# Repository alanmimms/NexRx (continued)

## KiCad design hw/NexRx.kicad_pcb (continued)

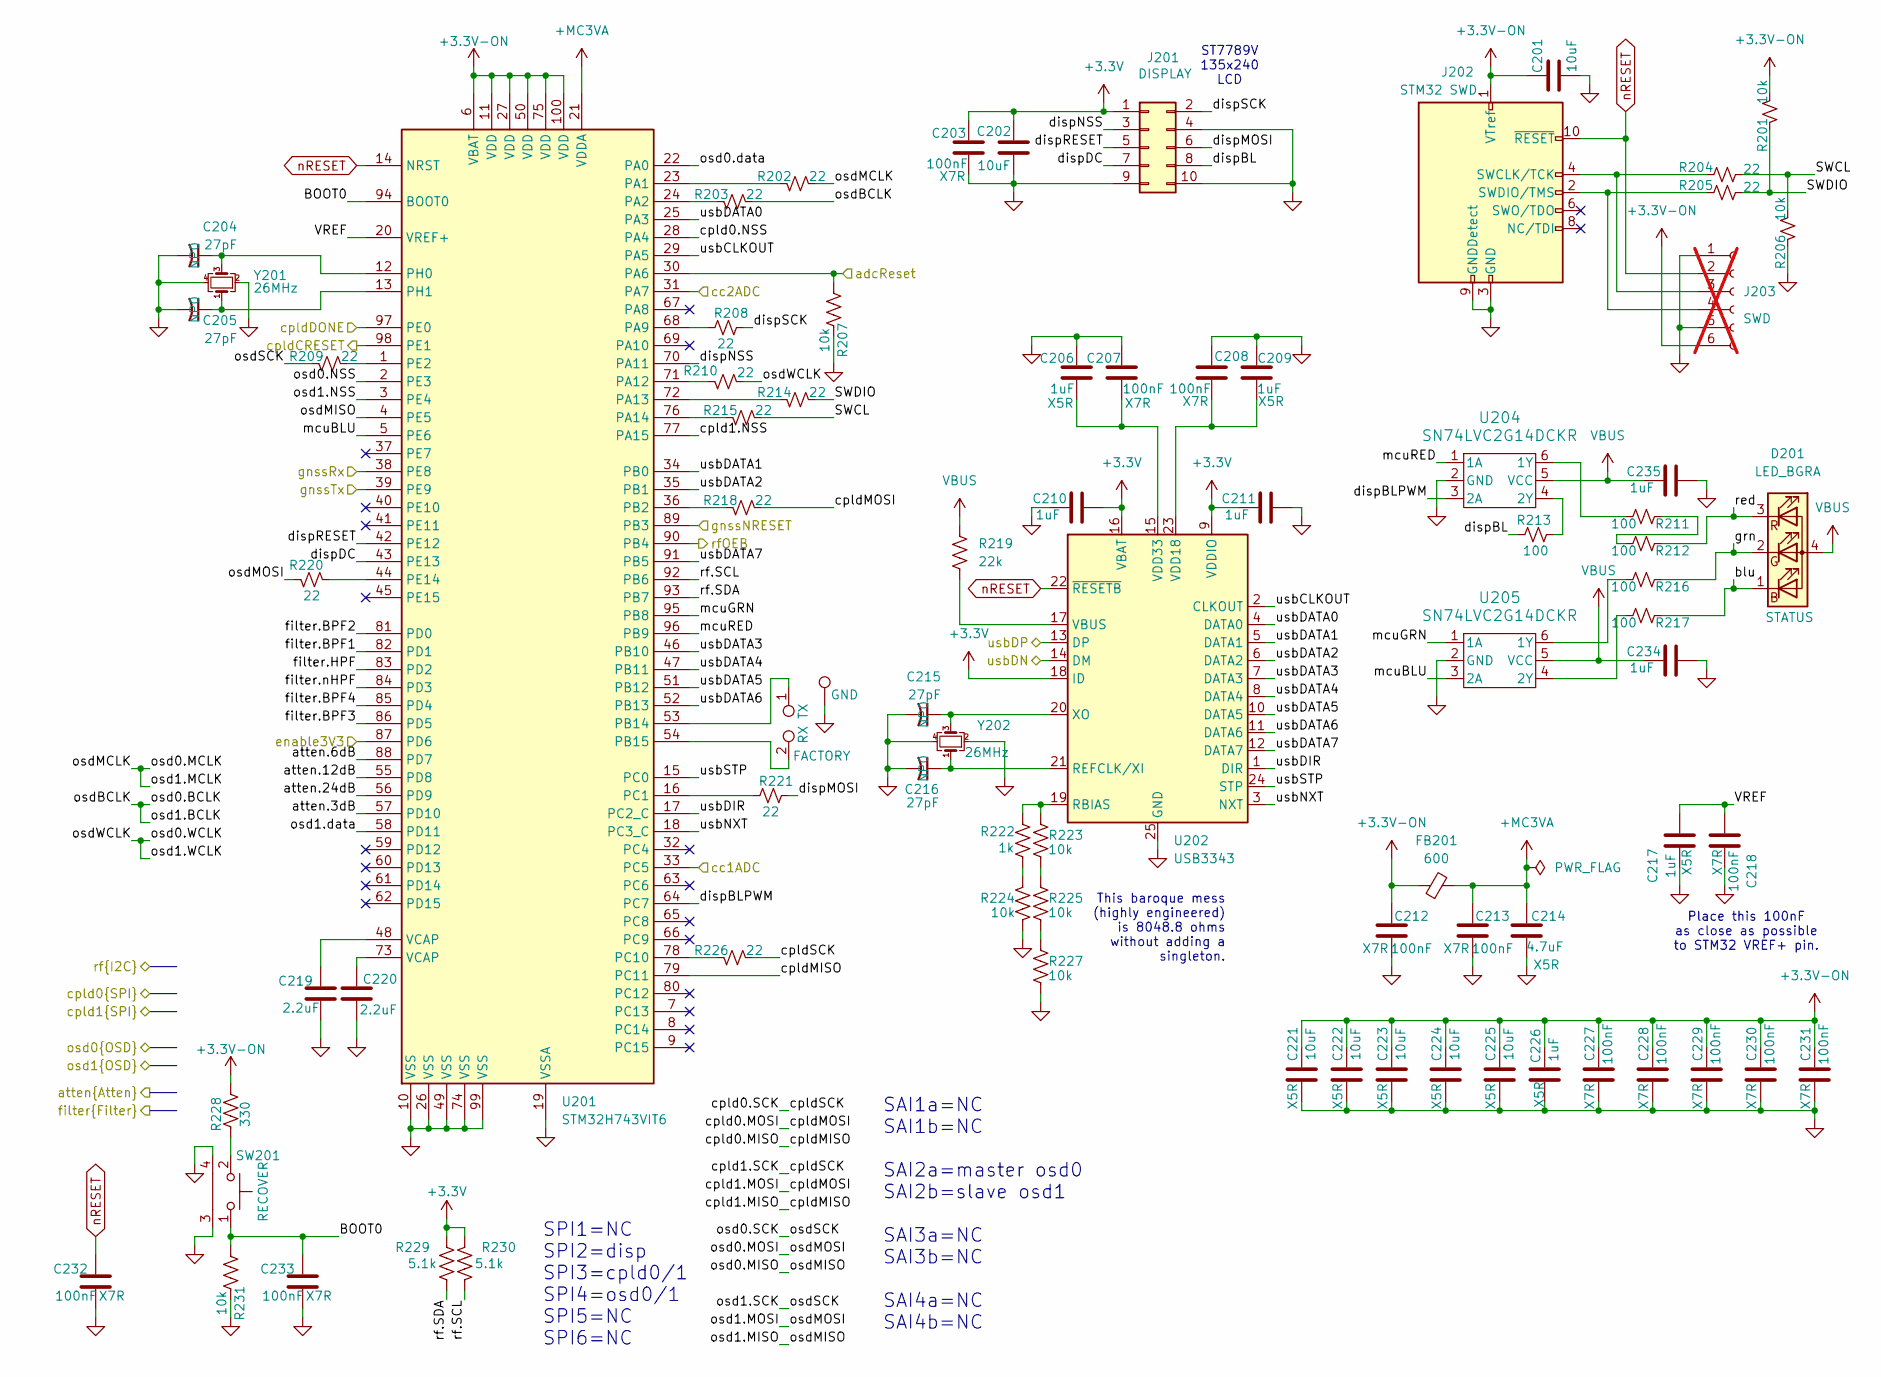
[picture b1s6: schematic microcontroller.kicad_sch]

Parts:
C201: 10uF; C_0402_1005Metric; MPN CL05A106MP6NUN8; LCSC_PN C76991
C202, C221, C222, C223, C224, C225: 10uF; C_0402_1005Metric; Mouser Part Number 187-CL05A106MP6NUN8
C203, C207, C208, C212, C213, C231: 100nF; C_0402_1005Metric; MPN GCM155R71H104KE02D; LCSC_PN C307331
C204: 27pF; C_0402_1005Metric; MPN 04023A270JAT2A; LCSC_PN C1557
C205, C215, C216: 27pF; C_0402_1005Metric; MPN 04023A270JAT2A; Mouser Part Number 581-04023A270JAT2A
C206, C209, C210, C211, C234, C235: 1uF; C_0402_1005Metric; Mouser Part Number 81-GRM155R61E105MA2D
C214: 4.7uF; C_0402_1005Metric; MPN CM05X5R475M10AH; LCSC_PN C23733
C217, C226: 1uF; C_0402_1005Metric; MPN GRM155R61E105MA12D; LCSC_PN C77009
C218, C227, C228, C229, C230, C232, C233: 100nF; C_0402_1005Metric; Mouser Part Number 81-GCM155R71H104KE2D
C219, C220: 2.2uF; C_0402_1005Metric; MPN TMK105CBJ225MV-F; LCSC_PN C12530
D201: LED_BGRA; WL-SFCD_0606; Mouser_PN 941-UHD1AA3K3E3V53Z3
FB201: 600; L_0603_1608Metric; MPN MI0603J601R-10; LCSC_PN C1006
J201: Conn_01x05_Pin; IDC-Header_2x05_P2.54mm_Vertical_SMD; LCSC_PN C32713285
J202: FTSH-105-01-L-DV-K; FTSH10501LDVK; MPN FTSH-105-01-L-DV-K; LCSC_PN C5155080
J203: SWD; PinHeader_1x06_P2.54mm_Vertical; not fitted
R201, R206, R207, R223, R224, R225, R227, R231: 10k; R_0402_1005Metric; MPN RT0402BRD0710KL; LCSC_PN C283961
R202, R203: 22; R_0402_1005Metric; MPN 560112110216; LCSC_PN C25092
R204, R205, R208, R209, R210, R214, R215, R218, R220, R221, R226: 22; R_0402_1005Metric; MPN 560112110216; JLCPCBpn C4258780
R211, R212, R213, R216, R217: 100; R_0402_1005Metric; MPN MCS04020C1000FE000; Mouser Part Number 594-MCS04020C1000FE0
R219: 22k; R_0402_1005Metric; LCSC_PN C25768
R222: 1k; R_0402_1005Metric; MPN RP0402FRE071KL; LCSC_PN C11702
R228: 330; R_0402_1005Metric; MPN RC0402JR-7D330RL; LCSC_PN C25104
R229, R230: 5.1k; R_0402_1005Metric; MPN AC0402FR-7W5K1L; LCSC_PN C854378
SW201: Push button switch; SW_TS11-674-43-BK-100-RA-D; LCSC_PN C7402553
TP201: GND; TestPoint_THTPad_1.0x1.0mm_Drill0.5mm
TP202: FACTORY; TestPoint_2Pads_Pitch2.54mm_Drill0.8mm
U201: STM32H743VIT6; LQFP-100_14x14mm_P0.5mm; MPN STM32H743VIT6; LCSC_PN C114409
U202: USB3343; QFN-24-1EP_4x4mm_P0.5mm_EP2.6x2.6mm; MPN USB3343-CP-TR; LCSC_PN C633347
U204, U205: SN74LVC2G14DCKR; SOIC_G14DCK3_TEX; LCSC_PN C37361
Y201, Y202: 26MHz; Crystal_SMD_2520-4Pin_2.5x2.0mm; MPN E2X260181G01; LCSC_PN C2149229

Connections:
+3.3V: C202.2, C203.1, C210.2, C211.1, J201.1, R229.1, R230.1, U202.9 (VDDIO), U202.16 (VBAT), U202.18 (ID); also elsewhere on the board
+3.3V-ON: C201.2, C212.1, C221.1, C222.1, C223.1, C224.1, C225.1, C226.1, C227.1, C228.1, C229.1, C230.1, C231.1, FB201.1, J202.1 (VTref), J203.6, R201.1, R228.1, U201.6 (VBAT), U201.11 (VDD), U201.27 (VDD), U201.50 (VDD), U201.75 (VDD), U201.100 (VDD); also elsewhere on the board
+MC3VA: C213.1, C214.1, FB201.2, U201.21 (VDDA)
/Clock/rf.SCL: R230.2, U201.92 (PB6); also elsewhere on the board
/Clock/rf.SDA: R229.2, U201.93 (PB7); also elsewhere on the board
/Clock/rfOEB: U201.90 (PB4); also elsewhere on the board
/Filters/en.BPF1: U201.82 (PD1); also elsewhere on the board
/Filters/en.BPF2: U201.81 (PD0); also elsewhere on the board
/Filters/en.BPF3: U201.86 (PD5); also elsewhere on the board
/Filters/en.BPF4: U201.85 (PD4); also elsewhere on the board
/Filters/en.HPF: U201.83 (PD2); also elsewhere on the board
/Filters/en.nHPF: U201.84 (PD3); also elsewhere on the board
/Power/cc1ADC: U201.33 (PC5); also elsewhere on the board
/Power/cc2ADC: U201.31 (PA7); also elsewhere on the board
/Power/enable3V3: U201.87 (PD6); also elsewhere on the board
/Power/usbDN: U202.14 (DM); also elsewhere on the board
/Power/usbDP: U202.13 (DP); also elsewhere on the board
/atten.3dB: U201.57 (PD10); also elsewhere on the board
/atten.6dB: U201.88 (PD7); also elsewhere on the board
/atten.12dB: U201.55 (PD8); also elsewhere on the board
/atten.24dB: U201.56 (PD9); also elsewhere on the board
/cpld0/cpld.NSS: U201.28 (PA4); also elsewhere on the board
/cpld0/cpldCRESET: U201.98 (PE1); also elsewhere on the board
/cpld0/cpldDONE: U201.97 (PE0); also elsewhere on the board
/cpld0/osd.NSS: U201.2 (PE3); also elsewhere on the board
/cpld0/osd.data: U201.22 (PA0); also elsewhere on the board
/cpld1/cpld.MISO: U201.79 (PC11); also elsewhere on the board
/cpld1/cpld.MOSI: R218.1; also elsewhere on the board
/cpld1/cpld.NSS: U201.77 (PA15); also elsewhere on the board
/cpld1/cpld.SCK: R226.1; also elsewhere on the board
/cpld1/osd.BCLK: R203.1; also elsewhere on the board
/cpld1/osd.MCLK: R202.1; also elsewhere on the board
/cpld1/osd.MISO: U201.4 (PE5); also elsewhere on the board
/cpld1/osd.MOSI: R220.2; also elsewhere on the board
/cpld1/osd.NSS: U201.3 (PE4); also elsewhere on the board
/cpld1/osd.SCK: R209.2; also elsewhere on the board
/cpld1/osd.WCLK: R210.2; also elsewhere on the board
/cpld1/osd.data: U201.58 (PD11); also elsewhere on the board
/microcontroller/BOOT0: C233.1, R231.1, SW201.1, U201.94 (BOOT0)
/microcontroller/SWCL: R204.2, R206.1, R215.1
/microcontroller/SWDIO: R201.2, R205.2, R214.1
/microcontroller/VREF: C217.1, C218.1, U201.20 (VREF+)
/microcontroller/adcReset: R207.1, U201.30 (PA6); also elsewhere on the board
/microcontroller/blu: D201.1 (BK), R217.1
/microcontroller/dispBL: J201.8, R213.2
/microcontroller/dispBLPWM: U201.64 (PC7), U204.3 (2A)
/microcontroller/dispDC: J201.7, U201.43 (PE13)
/microcontroller/dispMOSI: J201.6, R221.2
/microcontroller/dispNSS: J201.3, U201.70 (PA11)
/microcontroller/dispRESET: J201.5, U201.42 (PE12)
/microcontroller/dispSCK: J201.2, R208.2
/microcontroller/gnssNRESET: U201.89 (PB3); also elsewhere on the board
/microcontroller/gnssRx: U201.38 (PE8); also elsewhere on the board
/microcontroller/gnssTx: U201.39 (PE9); also elsewhere on the board
/microcontroller/grn: D201.2 (GK), R216.1
/microcontroller/mcuBLU: U201.5 (PE6), U205.3 (2A)
/microcontroller/mcuGRN: U201.95 (PB8), U205.1 (1A)
/microcontroller/mcuRED: U201.96 (PB9), U204.1 (1A)
/microcontroller/red: D201.3 (RK), R212.1
/microcontroller/usbCLKOUT: U201.29 (PA5), U202.2 (CLKOUT)
/microcontroller/usbDATA0: U201.25 (PA3), U202.4 (DATA0)
/microcontroller/usbDATA1: U201.34 (PB0), U202.5 (DATA1)
/microcontroller/usbDATA2: U201.35 (PB1), U202.6 (DATA2)
/microcontroller/usbDATA3: U201.46 (PB10), U202.7 (DATA3)
/microcontroller/usbDATA4: U201.47 (PB11), U202.8 (DATA4)
/microcontroller/usbDATA5: U201.51 (PB12), U202.10 (DATA5)
/microcontroller/usbDATA6: U201.52 (PB13), U202.11 (DATA6)
/microcontroller/usbDATA7: U201.91 (PB5), U202.12 (DATA7)
/microcontroller/usbDIR: U201.17 (PC2_C), U202.1 (DIR)
/microcontroller/usbNXT: U201.18 (PC3_C), U202.3 (NXT)
/microcontroller/usbSTP: U201.15 (PC0), U202.24 (STP)
GND: C201.1, C202.1, C203.2, C204.2, C205.2, C206.2, C207.1, C208.1, C209.2, C210.1, C211.2, C212.2, C213.2, C214.2, C215.2, C216.2, C217.2, C218.2, C219.2, C220.2, C221.2, C222.2, C223.2, C224.2, C225.2, C226.2, C227.2, C228.2, C229.2, C230.2, C231.2, C232.2, C233.2, C234.2, C235.2, J201.4, J201.9, J201.10, J202.3 (GND), J202.5 (GND), J202.9 (GNDDetect), J203.1, J203.5, R206.2, R207.2, R224.2, R227.2, R231.2, SW201.3 (GND), SW201.4 (GND), TP201.1, U201.10 (VSS), U201.19 (VSSA), U201.26 (VSS), U201.49 (VSS), U201.74 (VSS), U201.99 (VSS), U202.25 (GND), U204.2 (GND), U205.2 (GND), Y201.2, Y201.4, Y202.2, Y202.4; also elsewhere on the board
unnamed: C219.1, U201.48 (VCAP)
unnamed: C220.1, U201.73 (VCAP)
unnamed: J202.4 (SWCLK/TCK), J203.3, R204.1
unnamed: J202.2 (SWDIO/TMS), J203.4, R205.1
unnamed: R211.1, R212.2
unnamed: R222.2, R224.1
unnamed: R223.2, R225.1
unnamed: R225.2, R227.1
unnamed: R228.2, SW201.2
unnamed: R202.2, U201.23 (PA1)
unnamed: R203.2, U201.24 (PA2)
unnamed: R208.1, U201.68 (PA9)
unnamed: R210.1, U201.71 (PA12)
unnamed: R214.2, U201.72 (PA13)
unnamed: R215.2, U201.76 (PA14)
unnamed: R218.2, U201.36 (PB2)
unnamed: TP202.1, U201.53 (PB14)
unnamed: TP202.2, U201.54 (PB15)
unnamed: R221.1, U201.16 (PC1)
unnamed: R226.2, U201.78 (PC10)
unnamed: R209.1, U201.1 (PE2)
unnamed: R220.1, U201.44 (PE14)
unnamed: C204.1, U201.12 (PH0), Y201.3
unnamed: C205.1, U201.13 (PH1), Y201.1
unnamed: R222.1, R223.1, U202.19 (RBIAS)
unnamed: C216.1, U202.21 (REFCLK/XI), Y202.1
unnamed: R219.2, U202.17 (VBUS)
unnamed: C208.2, C209.1, U202.23 (VDD18)
unnamed: C206.1, C207.2, U202.15 (VDD33)
unnamed: C215.1, U202.20 (XO), Y202.3
unnamed: R211.2, U204.6 (1Y)
unnamed: R213.1, U204.4 (2Y)
unnamed: R216.2, U205.6 (1Y)
unnamed: R217.2, U205.4 (2Y)
VBUS: C234.1, C235.1, D201.4 (A), R219.1, U204.5 (VCC), U205.5 (VCC); also elsewhere on the board
nRESET: C232.1, J202.10 (~RESET), J203.2, U201.14 (NRST), U202.22 (~RESETB)

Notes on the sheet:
SPI1=NC SPI2=disp SPI3=cpld0/1 SPI4=osd0/1 SPI5=NC SPI6=NC
This baroque mess (highly engineered) is 8048.8 ohms without adding a singleton.
SAI1a=NC SAI1b=NC SAI2a=master osd0 SAI2b=slave osd1 SAI3a=NC SAI3b=NC SAI4a=NC SAI4b=NC
Place this 100nF as close as possible to STM32 VREF+ pin.
ST7789V 135x240 LCD

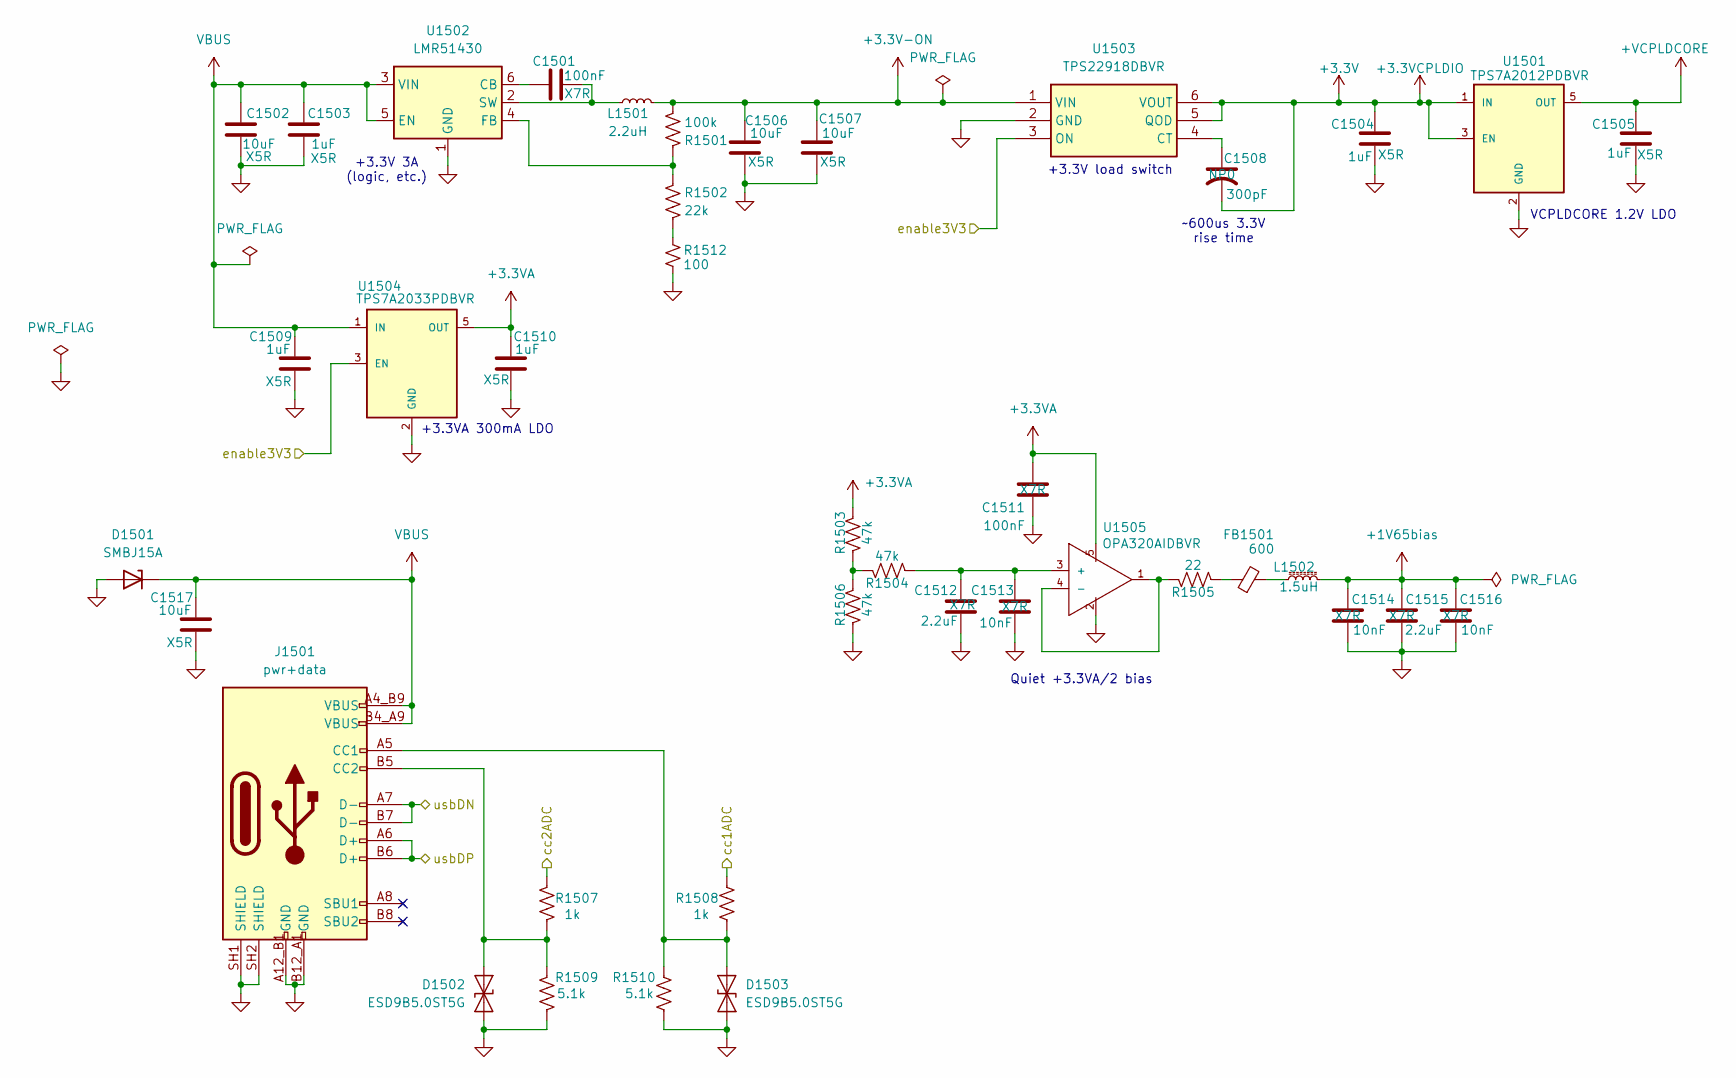
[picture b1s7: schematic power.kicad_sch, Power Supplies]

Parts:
C1501, C1511: 100nF; C_0402_1005Metric; MPN GCM155R71H104KE02D; LCSC_PN C307331
C1502, C1517: 10uF; C_0603_1608Metric; MPN CL10A106MA8NRWC; LCSC_PN C76614
C1503, C1505: 1uF; C_0402_1005Metric; MPN GRM155R61E105MA12D; LCSC_PN C77009
C1504, C1509, C1510: 1uF; C_0402_1005Metric; Mouser Part Number 81-GRM155R61E105MA2D
C1506, C1507: 10uF; C_0603_1608Metric; Mouser Part Number 187-CL10A106MA8NRWC
C1508: 300pF; C_0402_1005Metric; Mouser Part Number 80-C0402C301J3GACTU
C1512, C1515: 2.2uF; C_0402_1005Metric; MPN TMK105CBJ225MV-F; LCSC_PN C12530
C1513, C1514, C1516: 10nF; C_0402_1005Metric; MPN CC0402KRX5R8BB103; LCSC_PN C15195
D1501: SMBJ15A; D_SMB; MPN 1.0SMBJ15A-AQ; LCSC_PN C83846
D1502, D1503: ESD9B5.0ST5G; D_SOD-923; MPN ESD9B5.0ST5G; LCSC_PN C111566
FB1501: 600; L_0603_1608Metric; MPN MI0603J601R-10; LCSC_PN C1006
J1501: pwr+data; SAMESKY_UJ20-C-H-G-SMT-1-P16-TR; MPN UJ20-C-H-G-SMT-1-P16-TR; LCSC_PN C45082766
L1501: 2.2uH; L_0805_2012Metric; MPN 74479275222; LCSC_PN C341781
L1502: 1.5uH; L_0603_1608Metric; LCSC_PN C73201
R1501: 100k; R_0402_1005Metric; MPN RP0402BRD07100KL; LCSC_PN C25741
R1502: 22k; R_0402_1005Metric; LCSC_PN C25768
R1503, R1504, R1506: 47k; R_0402_1005Metric; MPN RC0402FR-7D47KL; JLCPCBpn C854337
R1505: 22; R_0402_1005Metric; MPN 560112110216; LCSC_PN C25092
R1507, R1508: 1k; R_0402_1005Metric; MPN RP0402FRE071KL; LCSC_PN C11702
R1509, R1510: 5.1k; R_0402_1005Metric; MPN AC0402FR-7W5K1L; LCSC_PN C854378
R1512: 100; R_0402_1005Metric; MPN MCS04020C1000FE000; Mouser Part Number 594-MCS04020C1000FE0
U1501: TPS7A2012PDBVR; DBV0005A-MFG; MPN TPS7A2012PDBVR; LCSC_PN C2864597
U1502: LMR51430; SOT-23-6; MPN MR51430YDDCR; LCSC_PN C5210749
U1503: TPS22918DBVR; SOT95P280X145-6N; MPN TPS22918DBVR; LCSC_PN C131941
U1504: TPS7A2033PDBVR; DBV0005A-MFG; MPN TPS7A2033PDBVR; LCSC_PN C2862740
U1505: OPA320AIDBVR; SOT95P280X145-5N; MPN OPA320AIDBVR; Mouser Part Number 595-OPA320AIDBVR

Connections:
+1V65bias: C1514.1, C1515.1, C1516.1, L1502.2; also elsewhere on the board
+3.3V: C1504.1, C1508.2, U1501.1 (IN), U1501.3 (EN), U1503.5 (QOD), U1503.6 (VOUT); also elsewhere on the board
+3.3V-ON: C1506.1, C1507.1, L1501.2, R1501.2, U1503.1 (VIN); also elsewhere on the board
+3.3VA: C1510.1, C1511.1, R1503.2, U1504.5 (OUT), U1505.5; also elsewhere on the board
+VCPLDCORE: C1505.1, U1501.5 (OUT); also elsewhere on the board
/Power/cc1ADC: R1508.1; also elsewhere on the board
/Power/cc2ADC: R1507.1; also elsewhere on the board
/Power/enable3V3: U1503.3 (ON), U1504.3 (EN); also elsewhere on the board
/Power/usbDN: J1501.A7 (D-), J1501.B7 (D-); also elsewhere on the board
/Power/usbDP: J1501.A6 (D+), J1501.B6 (D+); also elsewhere on the board
GND: C1502.2, C1503.2, C1504.2, C1505.2, C1506.2, C1507.2, C1509.2, C1510.2, C1511.2, C1512.2, C1513.2, C1514.2, C1515.2, C1516.2, C1517.2, D1501.2 (A), D1502.1 (A1), D1503.1 (A1), J1501.A12_B1 (GND), J1501.B12_A1 (GND), J1501.SH1 (SHIELD), J1501.SH2 (SHIELD), R1506.1, R1509.2, R1510.2, R1512.2, U1501.2 (GND), U1502.1 (GND), U1503.2 (GND), U1504.2 (GND), U1505.2; also elsewhere on the board
unnamed: D1502.2 (A2), J1501.B5 (CC2), R1507.2, R1509.1
unnamed: D1503.2 (A2), J1501.A5 (CC1), R1508.2, R1510.1
unnamed: FB1501.1, R1505.1
unnamed: FB1501.2, L1502.1
unnamed: R1502.1, R1512.1
unnamed: R1503.1, R1504.2, R1506.2
unnamed: C1501.1, U1502.6 (CB)
unnamed: R1501.1, R1502.2, U1502.4 (FB)
unnamed: C1501.2, L1501.1, U1502.2 (SW)
unnamed: C1508.1, U1503.4 (CT)
unnamed: C1512.1, C1513.1, R1504.1, U1505.3 (+)
unnamed: R1505.2, U1505.1, U1505.4 (-)
VBUS: C1502.1, C1503.1, C1509.1, C1517.1, D1501.1 (K), J1501.A4_B9 (VBUS), J1501.B4_A9 (VBUS), U1502.3 (VIN), U1502.5 (EN), U1504.1 (IN); also elsewhere on the board

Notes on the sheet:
~600us 3.3V rise time
VCPLDCORE 1.2V LDO
+3.3V load switch
Quiet +3.3VA/2 bias
+3.3V 3A (logic, etc.)
+3.3VA 300mA LDO

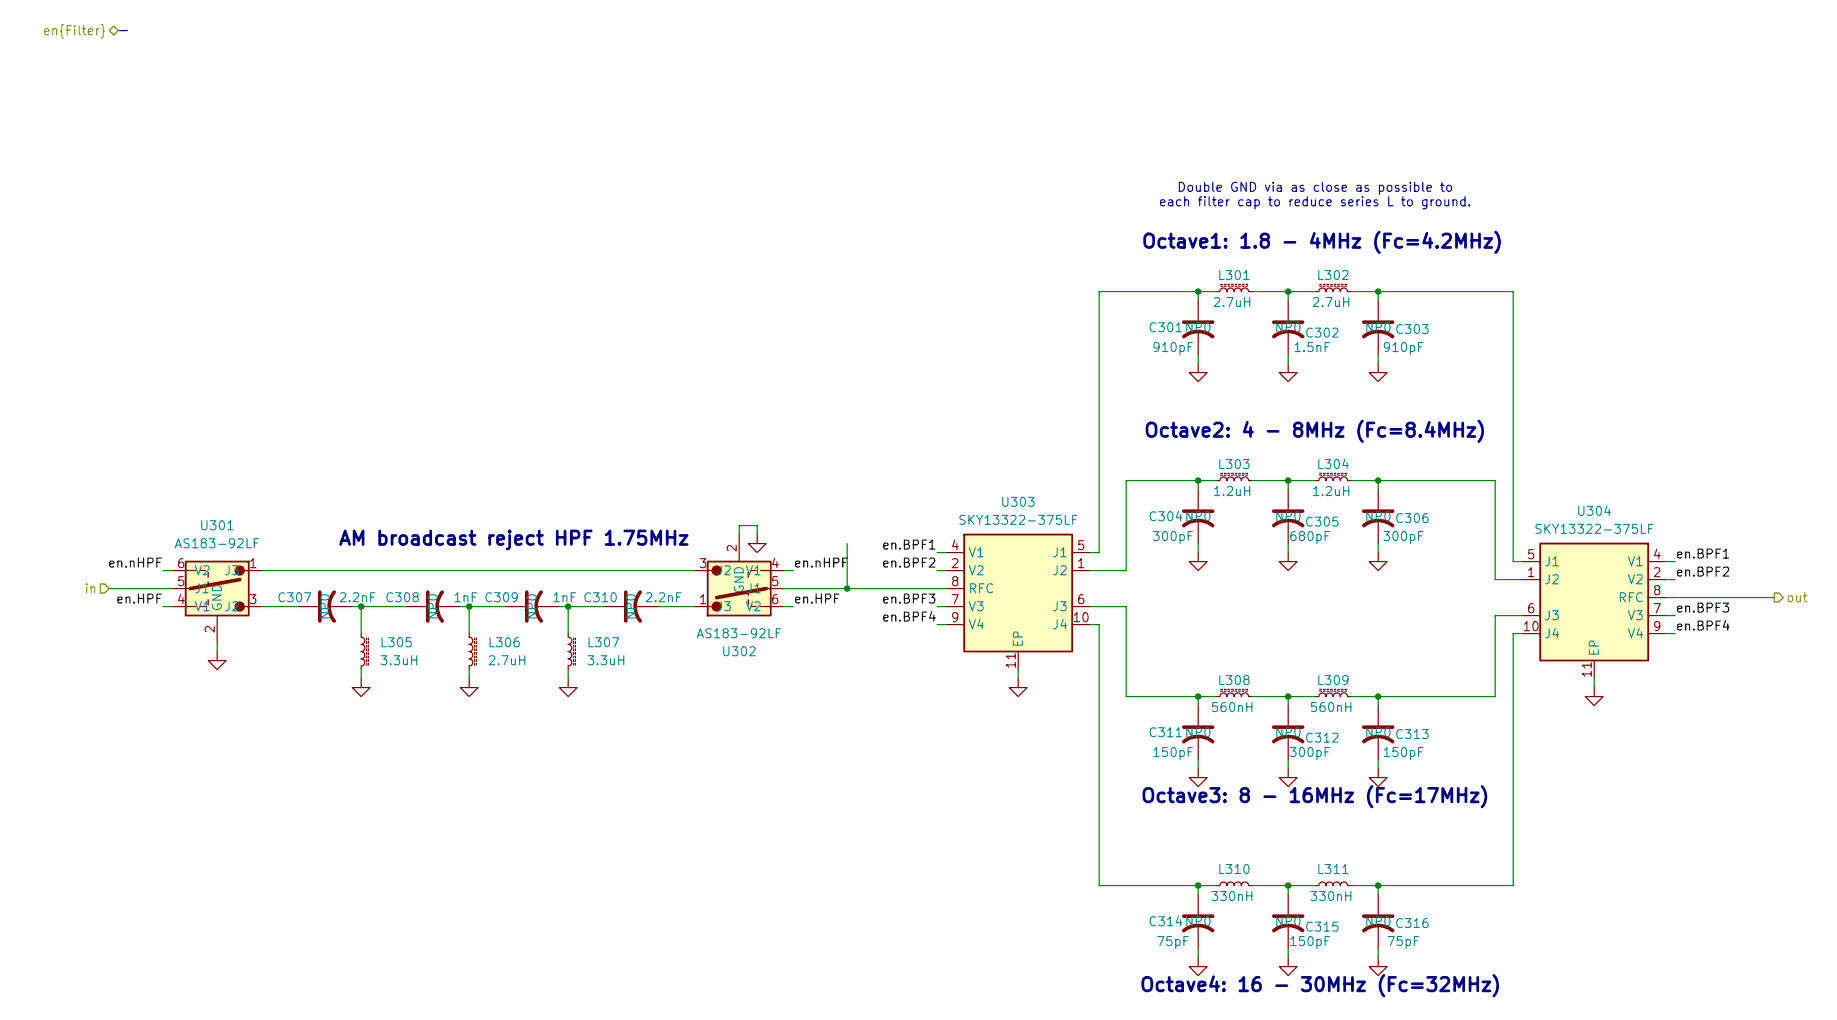
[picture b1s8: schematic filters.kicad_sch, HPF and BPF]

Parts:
C301, C303: 910pF; C_0603_1608Metric; Mouser Part Number 791-0603N911J250CT
C302: 1.5nF; C_0402_1005Metric; Mouser Part Number 80-C0402C152J3GACAUTO
C304, C306, C312: 300pF; C_0402_1005Metric; Mouser Part Number 80-C0402C301J3GACTU
C305: 680pF; C_0402_1005Metric; Mouser Part Number 81-GRT1555C1E681JA02J
C307, C310: 2.2nF; C_0402_1005Metric; Mouser Part Number 80-C0402C222K3GECTU
C308, C309: 1nF; C_0402_1005Metric; Mouser Part Number 81-GRT1555C1E102JA02J
C311, C313, C315: 150pF; C_0402_1005Metric; Mouser Part Number C0402C151J3GACTU
C314, C316: 75pF; C_0402_1005Metric; Mouser Part Number 80-CBR04C750G3GAC
L301, L302, L306: 2.7uH; L_1812_4532Metric; Mouser Part Number 994-1812CS-272XJRC
L303, L304: 1.2uH; L_1812_4532Metric; Mouser Part Number 994-1812CS-122XJRC
L305, L307: 3.3uH; L_1812_4532Metric; Mouser Part Number 994-1812CS-332XJRC
L308, L309: 560nH; L_1008_2520Metric_Pad1.43x2.20mm_HandSolder-keepout; Mouser Part Number 994-1008CS-561XJRC
L310, L311: 330nH; L_Coilcraft_2929SQ-331; MPN 2929SQ-331JEC; LCSC_PN C20623511
U301, U302: AS183-92LF; SOT65P220X110-6N; MPN AS183-92LF; LCSC_PN C2654768
U303, U304: SKY13322-375LF; SON50P200X300X50-11N-D; Mouser Part Number 873-SKY13322-375LF

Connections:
/Filters/en.BPF1: U303.4 (V1), U304.4 (V1); also elsewhere on the board
/Filters/en.BPF2: U303.2 (V2), U304.2 (V2); also elsewhere on the board
/Filters/en.BPF3: U303.7 (V3), U304.7 (V3); also elsewhere on the board
/Filters/en.BPF4: U303.9 (V4), U304.9 (V4); also elsewhere on the board
/Filters/en.HPF: U301.4 (V1), U302.6 (V2); also elsewhere on the board
/Filters/en.nHPF: U301.6 (V2), U302.4 (V1); also elsewhere on the board
/Filters/in: U301.5 (J1); also elsewhere on the board
/Filters/out: U304.8 (RFC); also elsewhere on the board
GND: C301.2, C302.2, C303.2, C304.2, C305.2, C306.2, C311.2, C312.2, C313.2, C314.2, C315.2, C316.2, L305.2, L306.2, L307.2, U301.2 (GND), U302.2 (GND), U303.11 (EP), U304.11 (EP); also elsewhere on the board
unnamed: C302.1, L301.2, L302.1
unnamed: C305.1, L303.2, L304.1
unnamed: C307.2, C308.1, L305.1
unnamed: C308.2, C309.1, L306.1
unnamed: C309.2, C310.1, L307.1
unnamed: C312.1, L308.2, L309.1
unnamed: C315.1, L310.2, L311.1
unnamed: C307.1, U301.3 (J2)
unnamed: U301.1 (J3), U302.3 (J2)
unnamed: U302.5 (J1), U303.8 (RFC)
unnamed: C310.2, U302.1 (J3)
unnamed: C301.1, L301.1, U303.5 (J1)
unnamed: C304.1, L303.1, U303.1 (J2)
unnamed: C311.1, L308.1, U303.6 (J3)
unnamed: C314.1, L310.1, U303.10 (J4)
unnamed: C303.1, L302.2, U304.5 (J1)
unnamed: C306.1, L304.2, U304.1 (J2)
unnamed: C313.1, L309.2, U304.6 (J3)
unnamed: C316.1, L311.2, U304.10 (J4)

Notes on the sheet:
Double GND via as close as possible to each filter cap to reduce series L to ground.
Octave3: 8 - 16MHz (Fc=17MHz)
Octave1: 1.8 - 4MHz (Fc=4.2MHz)
AM broadcast reject HPF 1.75MHz
Octave2: 4 - 8MHz (Fc=8.4MHz)
Octave4: 16 - 30MHz (Fc=32MHz)

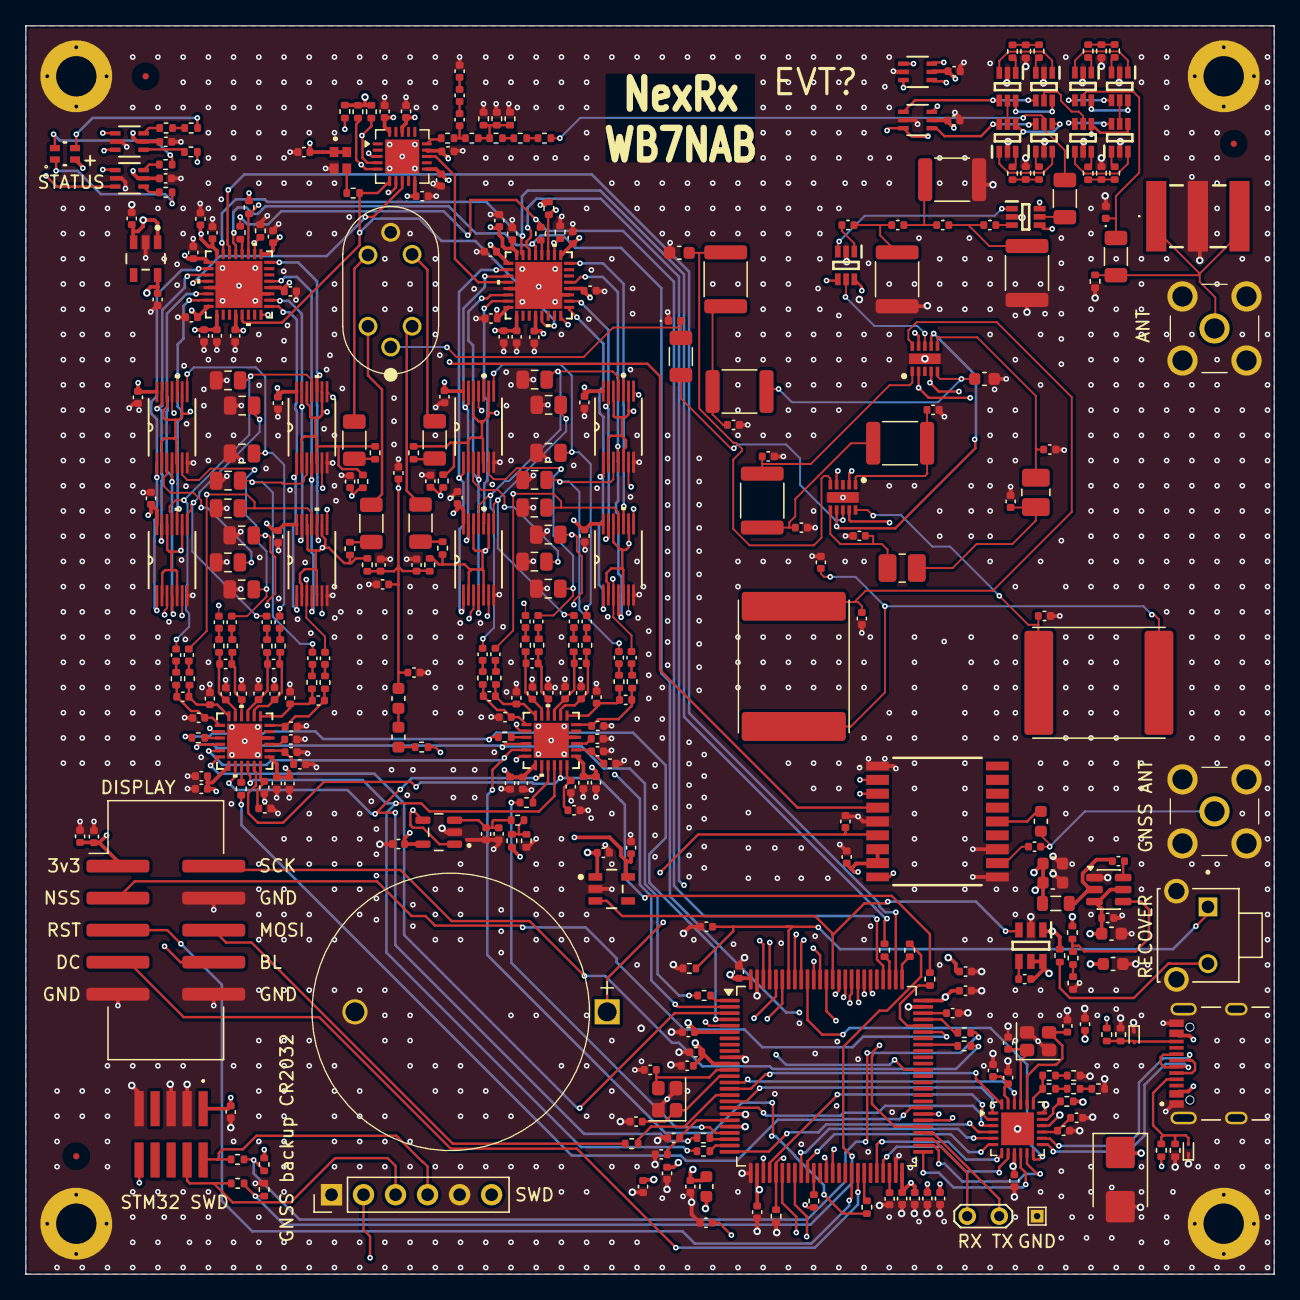
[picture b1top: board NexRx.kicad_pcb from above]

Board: 6 copper layers, 99.0 x 99.0 mm, 373 parts (0 on the bottom side), 276 nets.

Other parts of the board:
R501, R502: 16.5; R_0402_1005Metric
R503: 66.5; R_0402_1005Metric
R601, R602: 30.1; R_0402_1005Metric
R603: 26.7; R_0402_1005Metric
R701, R702: 44.2; R_0402_1005Metric
R703: 6.34; R_0402_1005Metric

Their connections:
GND: R503.2, R603.2, R703.2; also elsewhere on the board
unnamed: R501.1, R502.2, R503.1
unnamed: R601.1, R602.2, R603.1
unnamed: R701.1, R702.2, R703.1
unnamed 212: R501.2; also elsewhere on the board
unnamed 214: R502.1; also elsewhere on the board
unnamed 215: R601.2; also elsewhere on the board
unnamed 217: R602.1; also elsewhere on the board
unnamed 218: R701.2; also elsewhere on the board
unnamed 220: R702.1; also elsewhere on the board

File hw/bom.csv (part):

"Reference","Value","Footprint","QUANTITY","LCSC","MPN","Description"
"BT101","CR3032 holder","Library:S8401-46","1","C5904513","S8401-46 ","Coin Cell Battery Retainer, Vertical Throughboard, for CR2032 and BR2032 Coin Cell Batteries"
"C101","100nF","Capacitor_SMD:C_1206_3216Metric","1","","GRM3195C2A104JA01D","Capacitor, MLCC, NP0, 100V, 5%, 100nF, 1206"
"C102","100nF","Capacitor_SMD:C_1206_3216Metric","1","","GRM3195C2A104JA01D","Capacitor, MLCC, NP0, 100V, 5%, 100nF, 1206"
"C103","100nF","Capacitor_SMD:C_1206_3216Metric","1","","GRM3195C2A104JA01D","Capacitor, MLCC, NP0, 100V, 5%, 100nF, 1206"
"C104","10uF","Capacitor_SMD:C_0402_1005Metric","1","C479655","CM105X5R106M25AT","Unpolarized capacitor"
"C105","10uF","Capacitor_SMD:C_0402_1005Metric","1","C479655","CM105X5R106M25AT","Unpolarized capacitor"
"C106","150pF","Capacitor_SMD:C_0402_1005Metric","1","","","Unpolarized capacitor"
"C107","100nF","Capacitor_SMD:C_0402_1005Metric","1","","C0805F104K1RACAUTO","Capacitor, MLCC, X7R, 50V, 5%, 100nF, 0603"
"C108","100nF","Capacitor_SMD:C_0402_1005Metric","1","","C0805F104K1RACAUTO","Capacitor, MLCC, X7R, 50V, 5%, 100nF, 0603"
"C201","10uF","Capacitor_SMD:C_0402_1005Metric","1","","81-GXT155R71E223KE1D","Capacitor, MLCC, X7R, 25V, 10%, 10uF, 0603"
"C202","10uF","Capacitor_SMD:C_0402_1005Metric","1","","","Unpolarized capacitor"
"C203","10uF","Capacitor_SMD:C_0402_1005Metric","1","","81-GXT155R71E223KE1D","Capacitor, MLCC, X7R, 25V, 10%, 10uF, 0603"
"C204","27pF","Capacitor_SMD:C_0402_1005Metric","1","","","Capacitor, MLCC, NP0, 50V, 5%, 27pF, 0402"
"C205","27pF","Capacitor_SMD:C_0402_1005Metric","1","","","capacitor, small US symbol"
"C206","1uF","Capacitor_SMD:C_0402_1005Metric","1","","","Unpolarized capacitor"
"C207","100nF","Capacitor_SMD:C_0402_1005Metric","1","","C0805F104K1RACAUTO","Capacitor, MLCC, X7R, 50V, 5%, 100nF, 0603"
"C208","100nF","Capacitor_SMD:C_0402_1005Metric","1","","C0805F104K1RACAUTO","Capacitor, MLCC, X7R, 50V, 5%, 100nF, 0603"
"C209","1uF","Capacitor_SMD:C_0402_1005Metric","1","","","Unpolarized capacitor"
"C210","100nF","Capacitor_SMD:C_0402_1005Metric","1","","C0805F104K1RACAUTO","Capacitor, MLCC, X7R, 50V, 5%, 100nF, 0603"
"C211","100nF","Capacitor_SMD:C_0402_1005Metric","1","","C0805F104K1RACAUTO","Capacitor, MLCC, X7R, 50V, 5%, 100nF, 0603"
"C212","4.7uF","Capacitor_SMD:C_0402_1005Metric","1","","298D475X9010M2T","Capacitor, Tantalum, 10V, 10%, 4.7uF, 0805"
"C213","1uF","Capacitor_SMD:C_0402_1005Metric","1","","","Unpolarized capacitor"
"C214","1uF","Capacitor_SMD:C_0402_1005Metric","1","","","Unpolarized capacitor"
"C215","1uF","Capacitor_SMD:C_0402_1005Metric","1","","GRM155R61E105KE11D","Capacitor, MLCC, X5R, 25V, 10%, 1uF, 0402"
"C216","100nF","Capacitor_SMD:C_0402_1005Metric","1","","","Unpolarized capacitor"
"C217","27pF","Capacitor_SMD:C_0402_1005Metric","1","","","capacitor, small US symbol"
"C218","27pF","Capacitor_SMD:C_0402_1005Metric","1","","","capacitor, small US symbol"
"C219","2.2uF","Capacitor_SMD:C_0402_1005Metric","1","","","Capacitor, MLCC, X7R, 50V, 10%, 2.2uF, 0603"
"C220","2.2uF","Capacitor_SMD:C_0402_1005Metric","1","","","Capacitor, MLCC, X7R, 50V, 10%, 2.2uF, 0603"
"C221","10uF","Capacitor_SMD:C_0402_1005Metric","1","","","Unpolarized capacitor"
"C222","10uF","Capacitor_SMD:C_0402_1005Metric","1","","","Unpolarized capacitor"
"C223","10uF","Capacitor_SMD:C_0402_1005Metric","1","","","Unpolarized capacitor"
"C224","10uF","Capacitor_SMD:C_0402_1005Metric","1","","","Unpolarized capacitor"
"C225","10uF","Capacitor_SMD:C_0402_1005Metric","1","","","Unpolarized capacitor"
"C226","1uF","Capacitor_SMD:C_0402_1005Metric","1","","GRM155R61E105KE11D","Capacitor, MLCC, X5R, 25V, 10%, 1uF, 0402"
"C227","100nF","Capacitor_SMD:C_0402_1005Metric","1","","","Unpolarized capacitor"
"C228","100nF","Capacitor_SMD:C_0402_1005Metric","1","","","Unpolarized capacitor"
"C229","100nF","Capacitor_SMD:C_0402_1005Metric","1","","","Unpolarized capacitor"
"C230","100nF","Capacitor_SMD:C_0402_1005Metric","1","","","Unpolarized capacitor"
"C231","100nF","Capacitor_SMD:C_0402_1005Metric","1","","C0805F104K1RACAUTO","Capacitor, MLCC, X7R, 50V, 5%, 100nF, 0603"
"C232","100nF","Capacitor_SMD:C_0402_1005Metric","1","","","Unpolarized capacitor"
"C233","100nF","Capacitor_SMD:C_0402_1005Metric","1","","","Unpolarized capacitor"
"C301","910pF","Capacitor_SMD:C_0402_1005Metric","1","","C0402C132J5GACTU","capacitor, US symbol"
"C302","1.5nF","Capacitor_SMD:C_0402_1005Metric","1","","C0402C202J3GACTU","capacitor, US symbol"
"C303","910pF","Capacitor_SMD:C_0402_1005Metric","1","","C0402C132J5GACTU","capacitor, US symbol"
"C304","300pF","Capacitor_SMD:C_0402_1005Metric","1","","C0402C132J5GACTU","capacitor, US symbol"
"C305","620pF","Capacitor_SMD:C_0402_1005Metric","1","","C0402C202J3GACTU","capacitor, US symbol"
"C306","300pF","Capacitor_SMD:C_0402_1005Metric","1","","C0402C132J5GACTU","capacitor, US symbol"
"C307","2.2nF","Capacitor_SMD:C_0402_1005Metric","1","","GRM2165C1H162JA01D","capacitor, US symbol"
"C308","1nF","Capacitor_SMD:C_0402_1005Metric","1","","08051A911JAT2A","capacitor, US symbol"
"C309","1nF","Capacitor_SMD:C_0402_1005Metric","1","","08051A911JAT2A","capacitor, US symbol"
"C310","2.2nF","Capacitor_SMD:C_0402_1005Metric","1","","GRM2165C1H162JA01D","capacitor, US symbol"
"C311","150pF","Capacitor_SMD:C_0402_1005Metric","1","","C0402C132J5GACTU","capacitor, US symbol"
"C312","300pF","Capacitor_SMD:C_0402_1005Metric","1","","C0402C202J3GACTU","capacitor, US symbol"
"C313","150pF","Capacitor_SMD:C_0402_1005Metric","1","","C0402C132J5GACTU","capacitor, US symbol"
"C314","75pF","Capacitor_SMD:C_0402_1005Metric","1","","C0402C132J5GACTU","capacitor, US symbol"
"C315","160pF","Capacitor_SMD:C_0402_1005Metric","1","","C0402C202J3GACTU","capacitor, US symbol"
"C316","75pF","Capacitor_SMD:C_0402_1005Metric","1","","C0402C132J5GACTU","capacitor, US symbol"
"C317","100nF","Capacitor_SMD:C_0402_1005Metric","1","","C0805F104K1RACAUTO","Capacitor, MLCC, X7R, 50V, 5%, 100nF, 0603"
"C801","1uF","Capacitor_SMD:C_0402_1005Metric","1","","GRM155R61E105KE11D","Capacitor, MLCC, X5R, 25V, 10%, 1uF, 0402"
"C802","100nF","Capacitor_SMD:C_0402_1005Metric","1","","C0805F104K1RACAUTO","Capacitor, MLCC, X7R, 50V, 5%, 100nF, 0603"
"C803","100nF","Capacitor_SMD:C_0402_1005Metric","1","","C0805F104K1RACAUTO","Capacitor, MLCC, X7R, 50V, 5%, 100nF, 0603"
"C804","100nF","Capacitor_SMD:C_0402_1005Metric","1","","C0805F104K1RACAUTO","Capacitor, MLCC, X7R, 50V, 5%, 100nF, 0603"
"C805","10uF","Capacitor_SMD:C_0402_1005Metric","1","","TAJD106K050RNJ","Capacitor, Tantalum, 50V, 10%, 10uF, 0805"
"C806","4.7uF","Capacitor_SMD:C_0402_1005Metric","1","","","Capacitor, MLCC, X5R, 25V, 5%, 0402"
"C807","2.2nF","Capacitor_SMD:C_0402_1005Metric","1","","","Capacitor, MLCC, NP0, 25V, 5%, 0603"
"C808","10uF","Capacitor_SMD:C_0402_1005Metric","1","","TAJD106K050RNJ","Capacitor, Tantalum, 50V, 10%, 10uF, 0805"
"C809","100nF","Capacitor_SMD:C_0402_1005Metric","1","","C0805F104K1RACAUTO","Capacitor, MLCC, X7R, 50V, 5%, 100nF, 0603"
"C810","4.7uF","Capacitor_SMD:C_0402_1005Metric","1","","","Capacitor, MLCC, X5R, 25V, 5%, 0402"
"C811","100nF","Capacitor_SMD:C_0402_1005Metric","1","","C0805F104K1RACAUTO","Capacitor, MLCC, X7R, 50V, 5%, 100nF, 0603"
"C812","10uF","Capacitor_SMD:C_0402_1005Metric","1","","TAJD106K050RNJ","Capacitor, Tantalum, 50V, 10%, 10uF, 0805"
"C813","150pF","Capacitor_SMD:C_0402_1005Metric","1","","06033A151FAT2A","Capacitor, MLCC, NP0, 50V, 5%, 150pF, 0603"
"C814","150pF","Capacitor_SMD:C_0402_1005Metric","1","","06033A151FAT2A","Capacitor, MLCC, NP0, 50V, 5%, 150pF, 0603"
"C815","8nF 1%","Capacitor_SMD:C_0805_2012Metric","1","","","Unpolarized capacitor"
"C816","1uF","Capacitor_SMD:C_0402_1005Metric","1","","GRM155R61E105KE11D","Capacitor, MLCC, X5R, 25V, 10%, 1uF, 0402"
"C817","8nF 1%","Capacitor_SMD:C_0805_2012Metric","1","","","Unpolarized capacitor"
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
